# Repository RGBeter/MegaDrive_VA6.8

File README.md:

# MegaDrive
An Open-Source HardWare (OSHW) recreation of the rare Sega Mega Drive VA6.8

The design tries to be a 1:1 recreation of the original IC BD M5 PAL V6.8 board.

## Changes and Notes
- PCB altered to use surface mount MB3514

- Original VA6.8 did not populate C30, despite the MB3514 having a mono audio buffer

- Some capacitor values may be inaccurate in the video section

## Tips if you decide to make this/get it made
The dimensions are 240x191mm.

You will have to source the 2 SEGA custom chips from either a dead board or a chip dealer.

## Credits

ArcadeTV for the stripped scans:
https://circuit-board.de/forum/index.php/Thread/13913-STRIP-CLUB-PCB-Scans/
StonedDiscord for original Mega Drive Pal VA5-6.5 reproduction PCB

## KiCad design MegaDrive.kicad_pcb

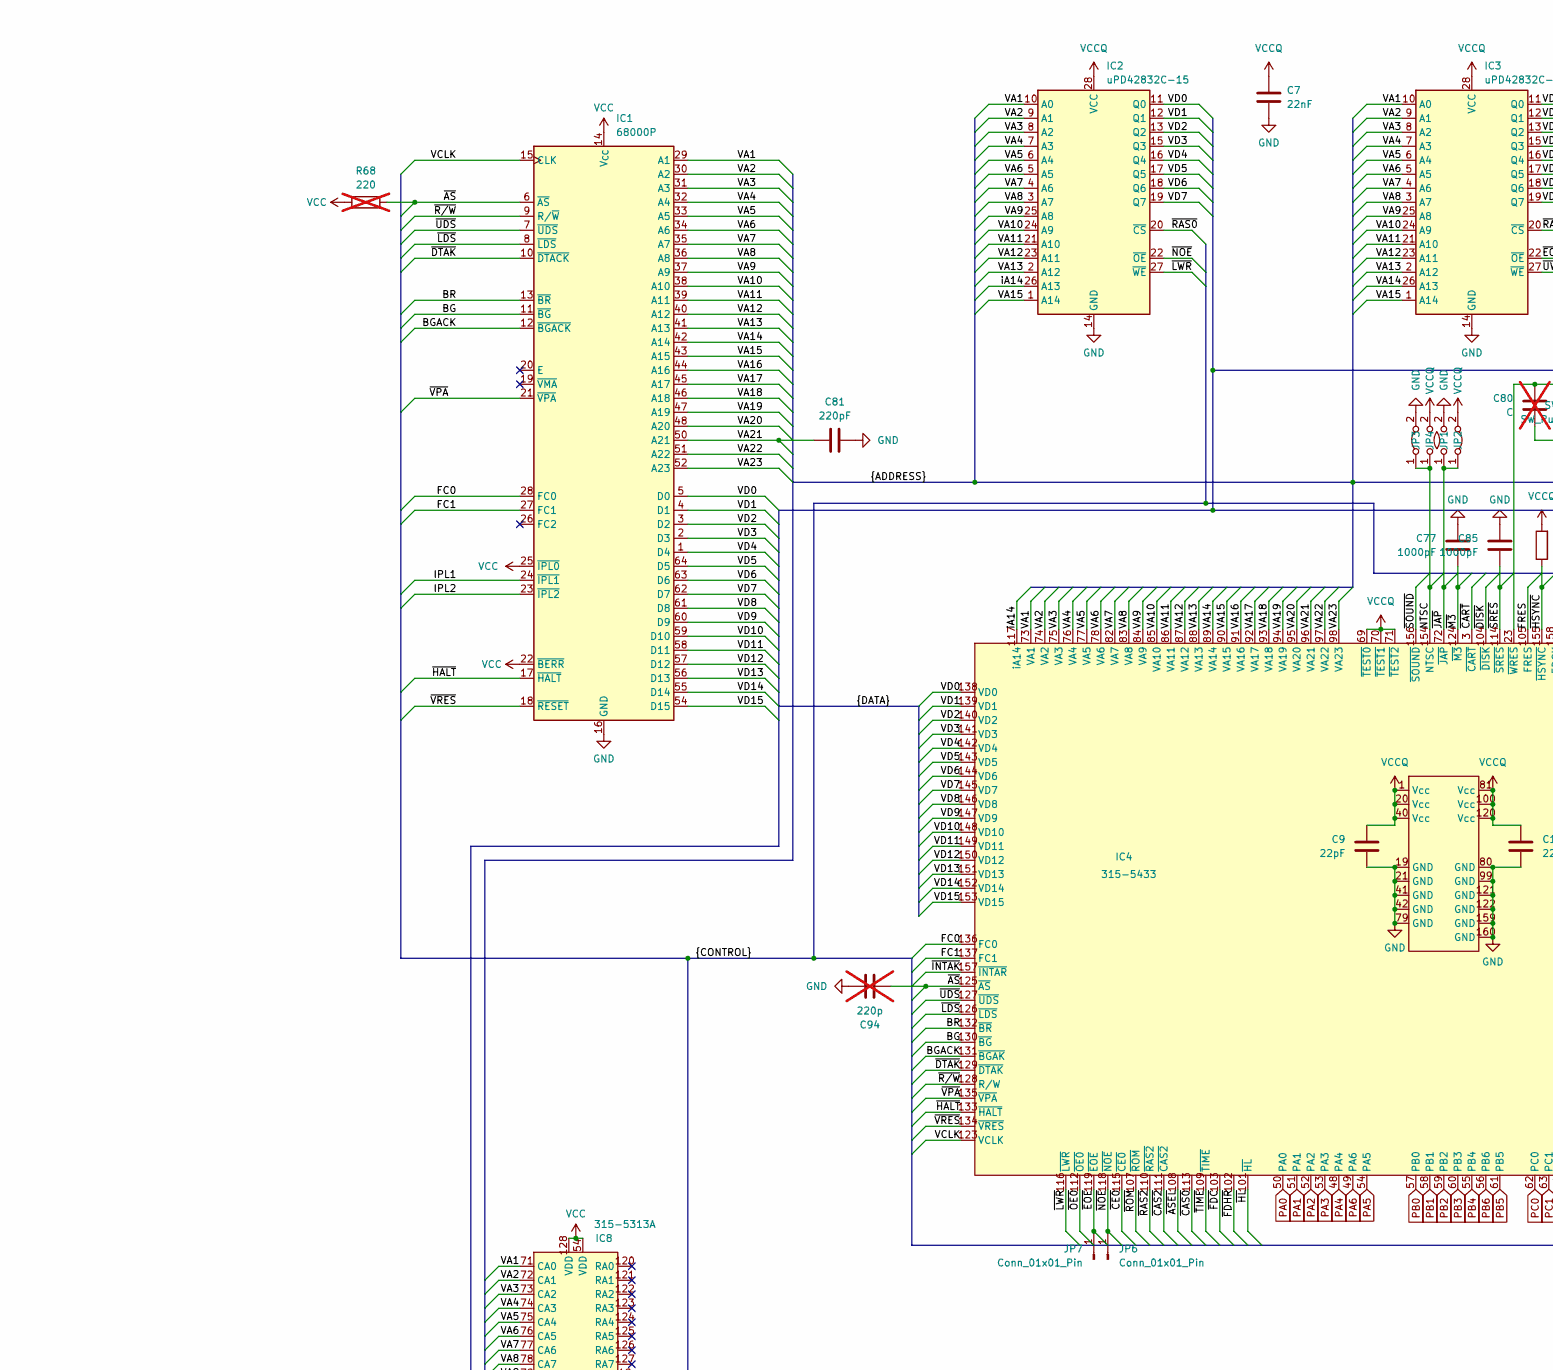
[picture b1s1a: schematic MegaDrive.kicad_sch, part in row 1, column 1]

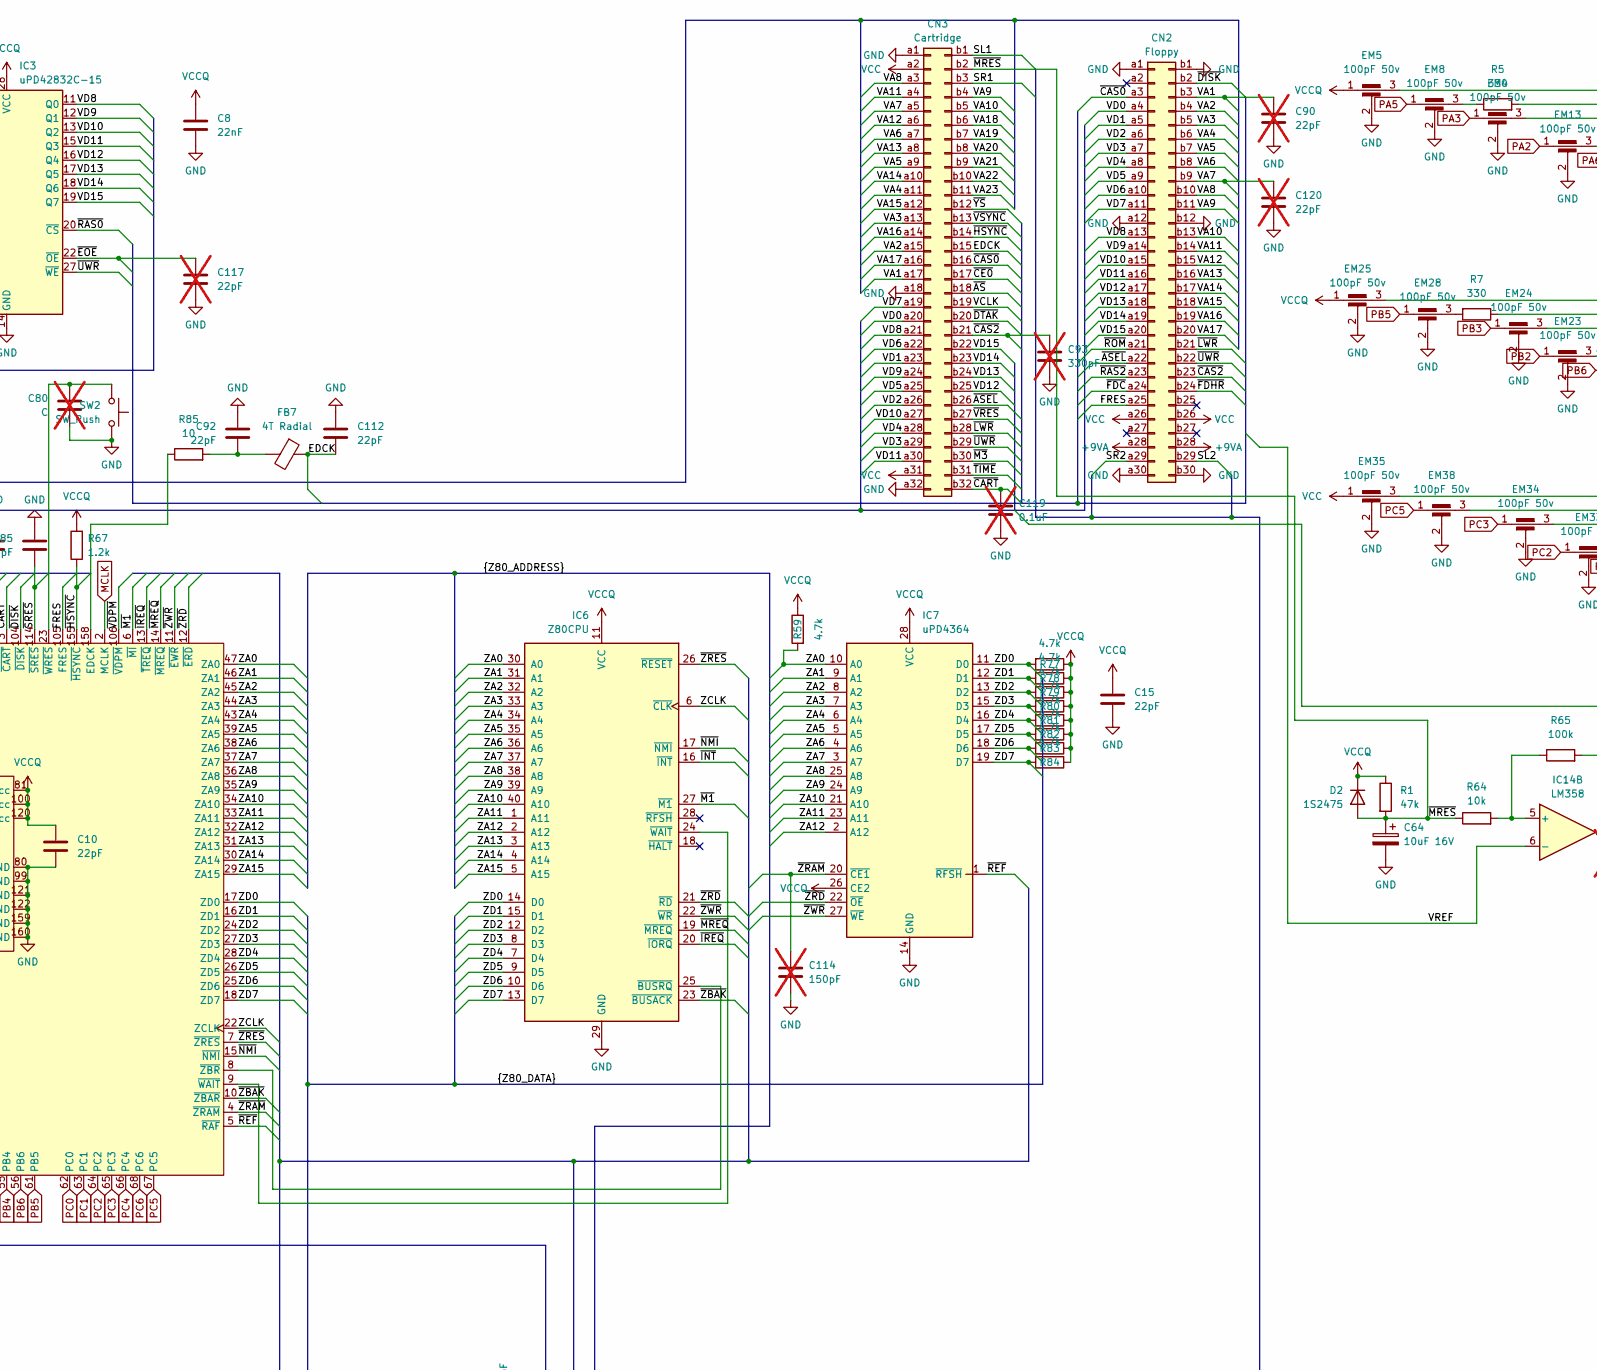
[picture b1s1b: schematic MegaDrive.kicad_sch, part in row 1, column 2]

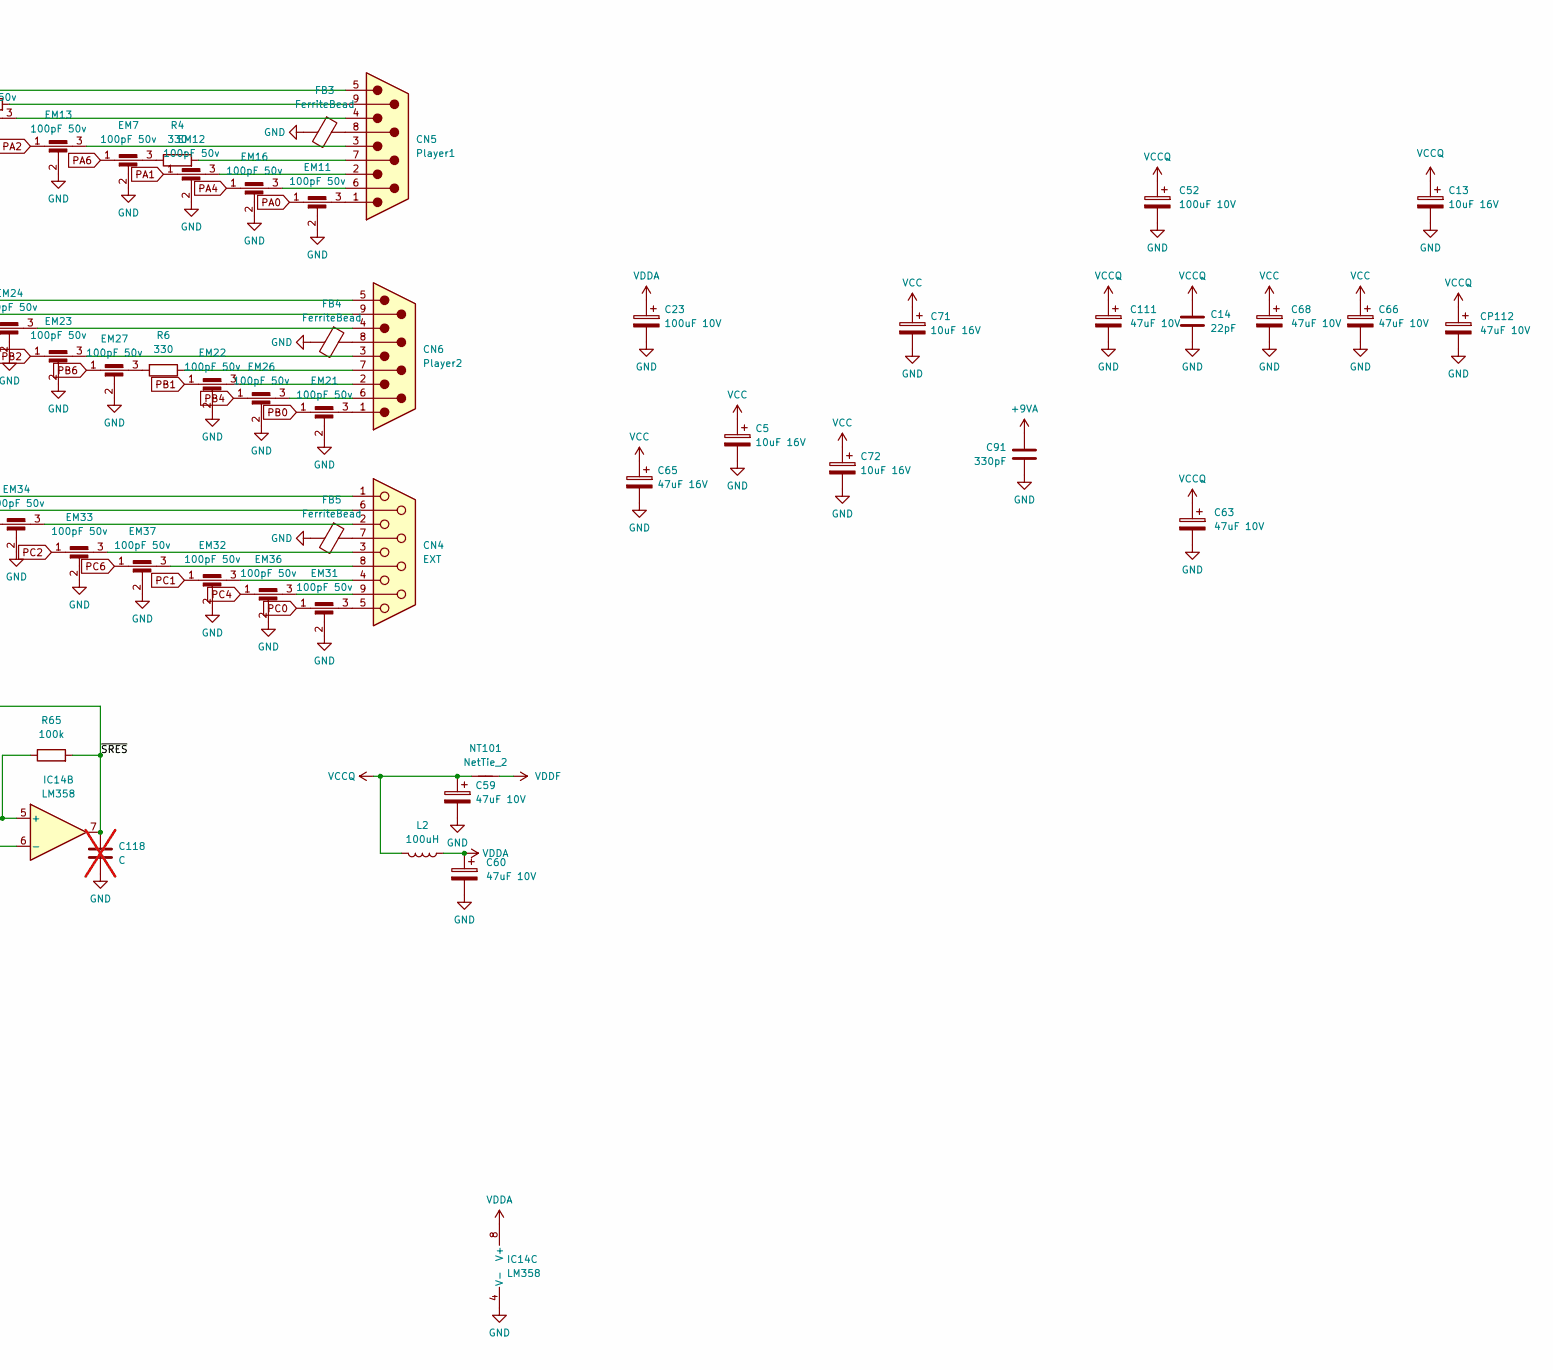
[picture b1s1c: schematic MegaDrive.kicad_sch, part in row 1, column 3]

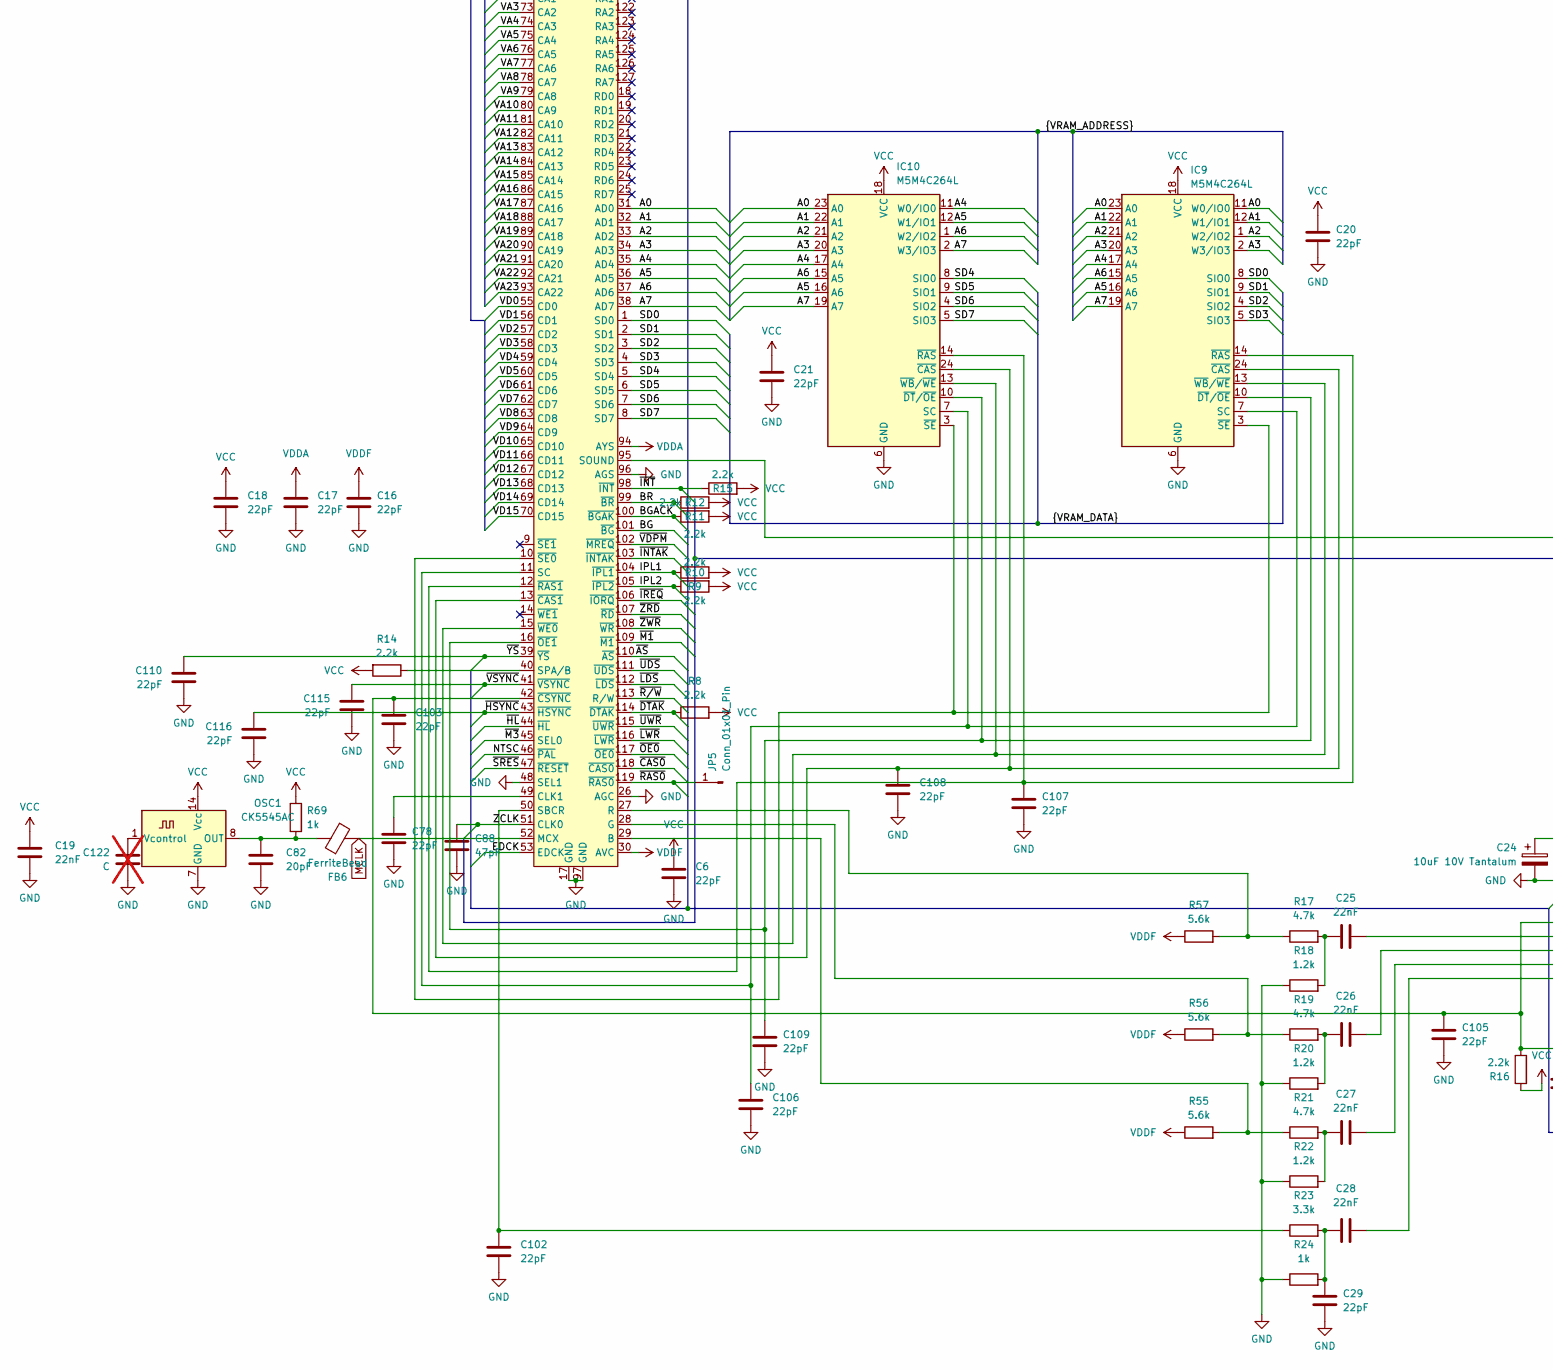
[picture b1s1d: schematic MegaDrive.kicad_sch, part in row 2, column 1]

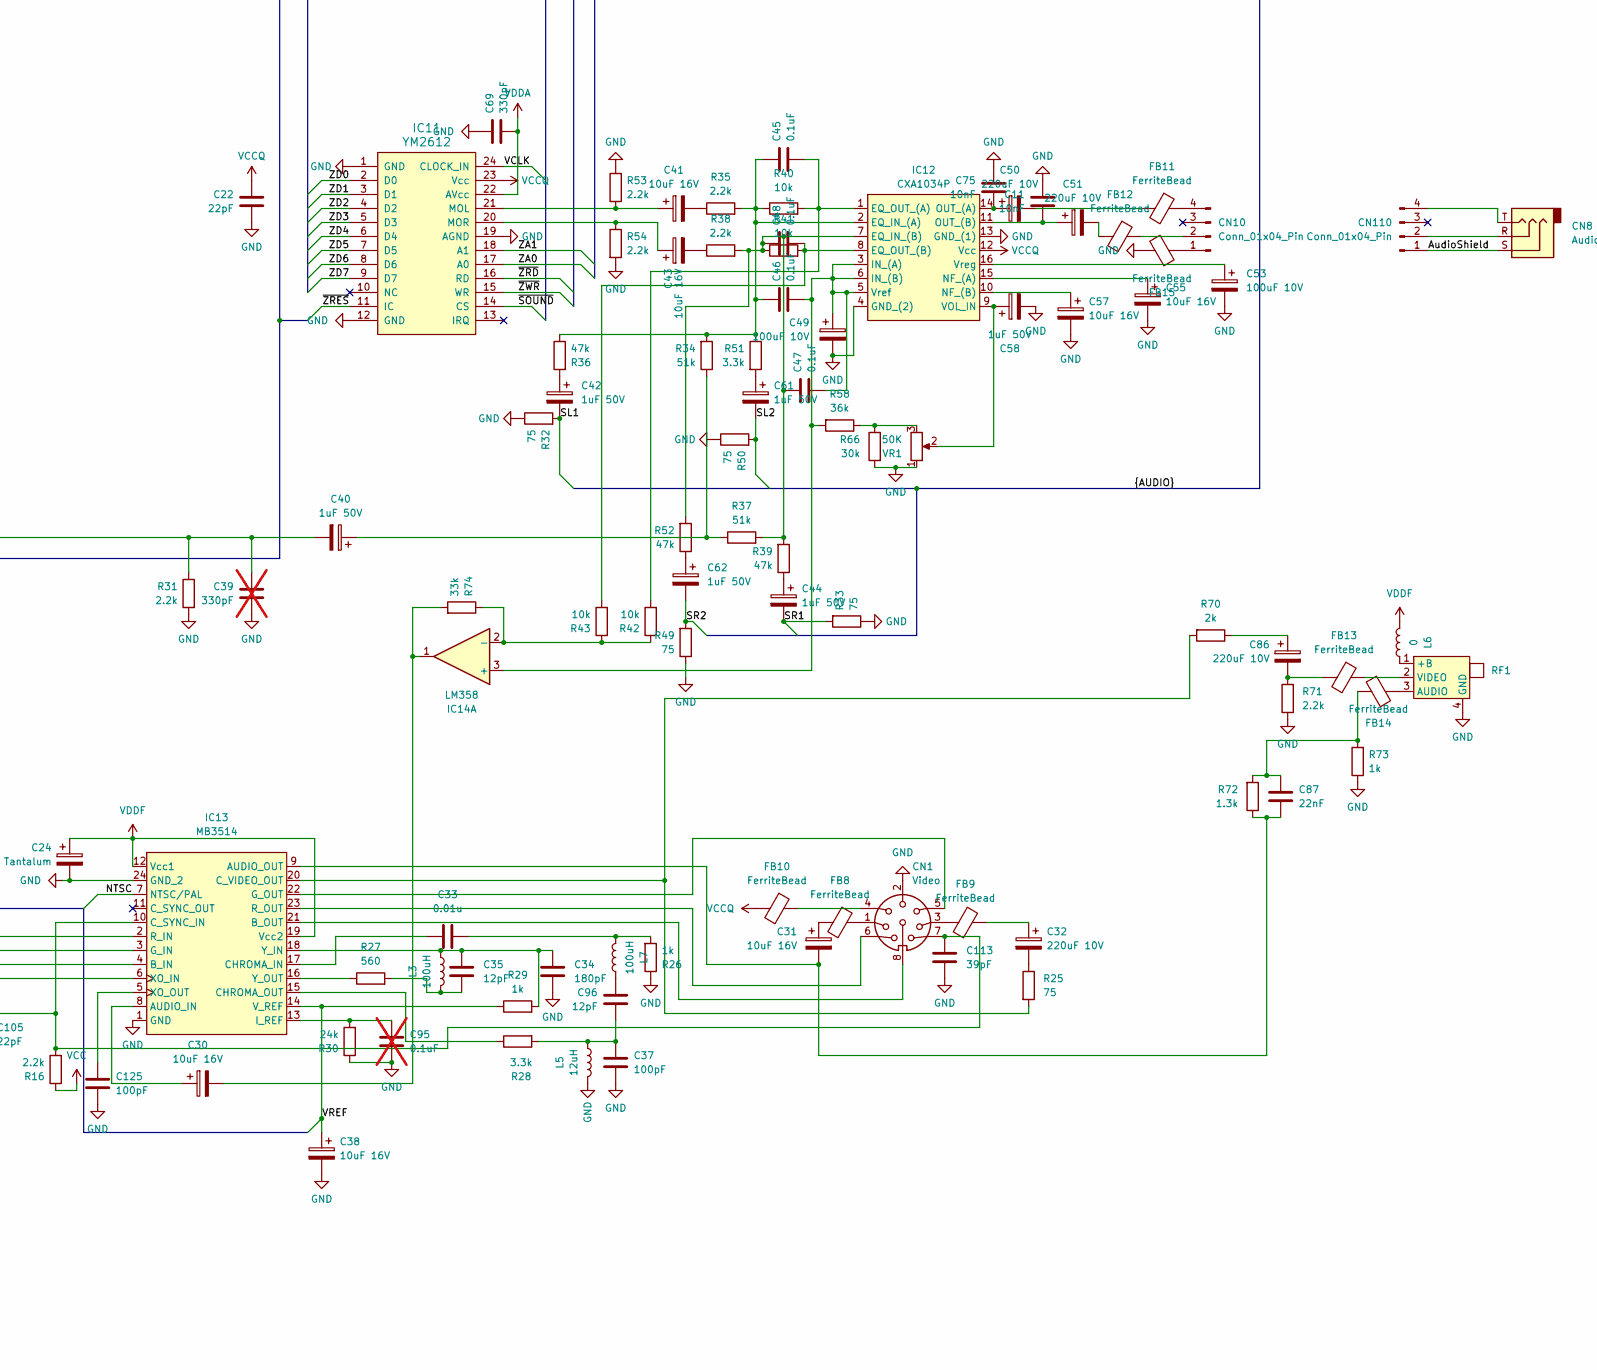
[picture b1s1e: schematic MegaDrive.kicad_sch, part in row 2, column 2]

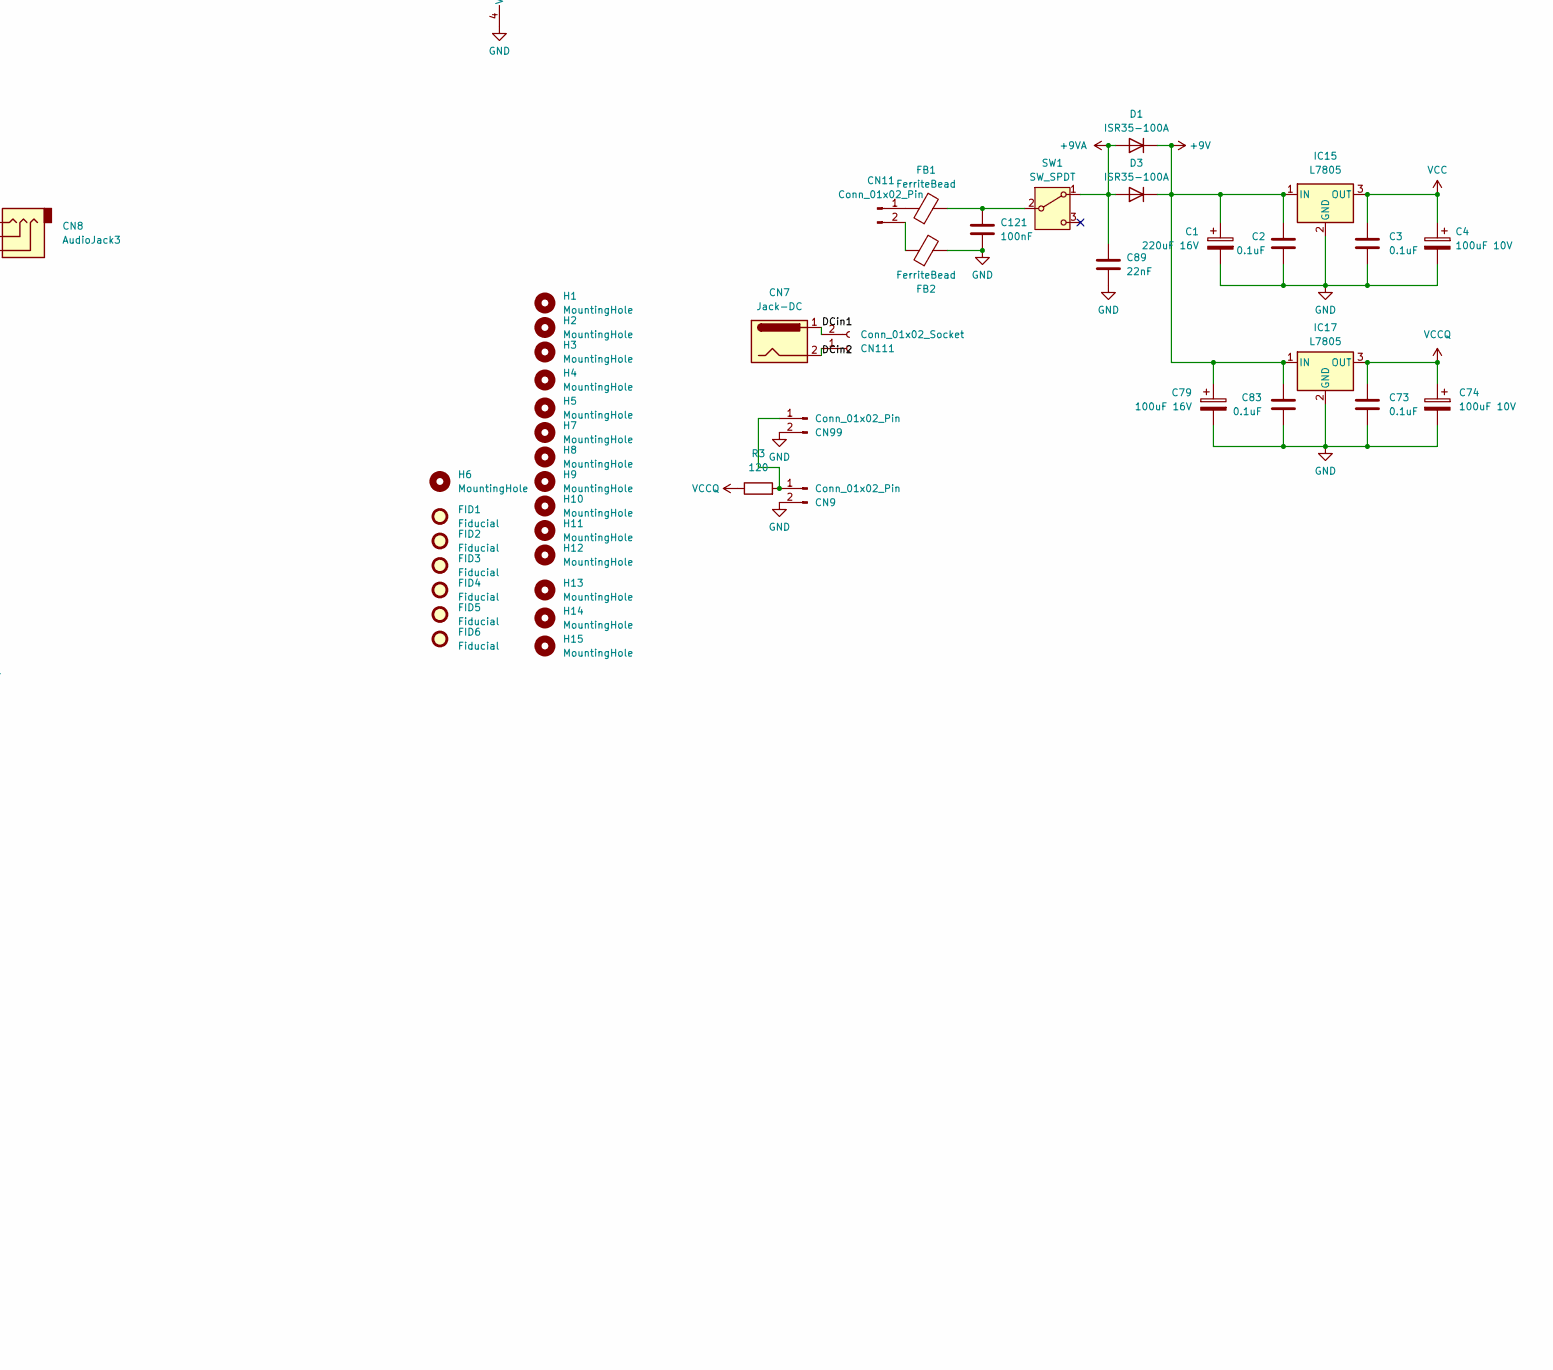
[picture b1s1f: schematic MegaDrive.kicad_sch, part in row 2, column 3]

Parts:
C1: 220uF 16V; CP_Radial_Tantal_D4.5mm_P5.00mm
C2, C3, C45, C46, C47, C48, C73, C83: 0.1uF; C_0805_2012Metric
C4, C23, C49, C52, C53, C74: 100uF 10V; CP_Radial_Tantal_D4.5mm_P5.00mm
C5, C13, C30, C31, C38, C41, C43, C55, C57, C64, C71, C72: 10uF 16V; CP_Radial_Tantal_D4.5mm_P5.00mm
C6, C9, C10, C14, C15, C16, C17, C18, C20, C21, C22, C29, C78, C92, C102, C103, C105, C106, C107, C108, C109, C110, C112, C115, C116: 22pF; C_0805_2012Metric
C7, C8, C19, C25, C26, C27, C28, C87, C89: 22nF; C_0805_2012Metric
C11, C75: 10nF; C_0805_2012Metric
C24: 10uF 10V Tantalum; CP_Radial_Tantal_D4.5mm_P5.00mm
C32, C50, C51, C86: 220uF 10V; CP_Radial_Tantal_D4.5mm_P5.00mm
C33: 0.01u; C_0805_2012Metric
C34: 180pF; C_0805_2012Metric
C35, C96: 12pF; C_0805_2012Metric
C37, C125: 100pF; C_0805_2012Metric
C39, C93: 330pF; C_0805_2012Metric; not fitted
C40, C42, C44, C58, C61, C62: 1uF 50V; CP_Radial_Tantal_D4.5mm_P5.00mm
C59, C60, C63, C66, C68, C111: 47uF 10V; CP_Radial_Tantal_D4.5mm_P5.00mm
C65: 47uF 16V; CP_Radial_Tantal_D4.5mm_P5.00mm
C69, C91: 330pF; C_0805_2012Metric
C77, C85: 1000pF; C_0805_2012Metric
C79: 100uF 16V; CP_Radial_Tantal_D4.5mm_P5.00mm
C80, C118, C122: C; C_0805_2012Metric; not fitted
C81: 220pF; C_0805_2012Metric
C82: 20pF; C_0805_2012Metric
C88: 47pF; C_0805_2012Metric
C90, C117, C120: 22pF; C_0805_2012Metric; not fitted
C94: 220p; C_0805_2012Metric; not fitted
C95, C119: 0.1uF; C_0805_2012Metric; not fitted
C113: 39pF; C_0805_2012Metric
C114: 150pF; C_0805_2012Metric; not fitted
C121: 100nF; C_0805_2012Metric
CN1: Video; DIN8Video
CN2: Floppy; Expansion
CN3: Cartridge; SEGA_2x32_Female_Vertical_THT
CN4: EXT; DSUB-9_Socket_Horizontal_P2.77x2.84mm_EdgePinOffset9.40mm
CN5: Player1; DSUB-9_Pins_Horizontal_P2.77x2.84mm_EdgePinOffset9.40mm
CN6: Player2; DSUB-9_Pins_Horizontal_P2.77x2.84mm_EdgePinOffset9.40mm
CN7: Jack-DC; BarrelJack_CUI_PJ-002A_Horizontal
CN8: AudioJack3; Jack_3.5mm
CN9, CN99: Conn_01x02_Pin; PinSocket_1x02_P2.54mm_Vertical
CN10, CN110: Conn_01x04_Pin; PinHeader_1x04_P2.00mm_Vertical
CN11: Conn_01x02_Pin; PinHeader_1x02_P2.54mm_Vertical
CN111: Conn_01x02_Socket; PinHeader_1x02_P2.54mm_Vertical
CP112: 47uF 10V; CP_Radial_Tantal_D4.5mm_P5.00mm
D1, D3: ISR35-100A; D_A-405_P5.08mm_Vertical_AnodeUp
D2: 1S2475; D_A-405_P5.08mm_Vertical_AnodeUp
EM4, EM5, EM7, EM8, EM11, EM12, EM13, EM16, EM21, EM22, EM23, EM24, EM25, EM26, EM27, EM28, EM31, EM32, EM33, EM34, EM35, EM36, EM37, EM38: 100pF 50v; Resonator-3Pin_W6.0mm_H3.0mm
FB1, FB2, FB3, FB4, FB5, FB8, FB9, FB10, FB13, FB14: FerriteBead; L_Axial_L7.0mm_D3.3mm_P5.08mm_Vertical_Fastron_MICC
FB6, FB11, FB12, FB15: FerriteBead; LairdTech_28C0236-0JW-10
FB7: 4T Radial; LairdTech_28C0236-0JW-10
FID1, FID2, FID3, FID4, FID5, FID6: Fiducial; Fiducial_1.5mm_Mask4.5mm
H1, H2, H3, H4, H5, H7, H8, H9, H10, H11, H12: MountingHole; MountingHole_3.2mm_M3
H6: MountingHole; MountingHole_4mm
H13, H14, H15: MountingHole; MountingHole_5mm
IC1: 68000P; DIP-64_W22.86mm
IC2, IC3: uPD42832C-15; DIP-28_DoubleLast
IC4: 315-5433; QFP-160_28x28_Pitch0.65mm
IC6: Z80CPU; DIP-40_W15.24mm
IC7: uPD4364; DIP-28_DoubleFirst
IC8: 315-5313A; QFP128
IC9, IC10: M5M4C264L; ZIP-24
IC11: YM2612; DIP-24_W15.24mm
IC12: CXA1034P; DIP-16_W7.62mm
IC13: MB3514; SOIC-24_CXA
IC14: LM358; DIP-8_W7.62mm
IC15, IC17: L7805; TO-220-3_Vertical
JP1: JAP; R_Axial_DIN0204_L3.6mm_D1.6mm_P5.08mm_Horizontal
JP2: ENG; R_Axial_DIN0204_L3.6mm_D1.6mm_P5.08mm_Horizontal
JP3: PAL; R_Axial_DIN0204_L3.6mm_D1.6mm_P5.08mm_Horizontal
JP4: NTSC; R_Axial_DIN0204_L3.6mm_D1.6mm_P5.08mm_Horizontal
JP5, JP6, JP7: Conn_01x01_Pin; PinSocket_1x01_P2.54mm_Vertical
L2, L3, L7: 100uH; R_Axial_DIN0204_L3.6mm_D1.6mm_P5.08mm_Horizontal
L5: 12uH; R_Axial_DIN0204_L3.6mm_D1.6mm_P5.08mm_Horizontal
L6: 0; L_Axial_L7.0mm_D3.3mm_P5.08mm_Vertical_Fastron_MICC
NT101: NetTie_2; NetTie-2_SMD_Pad2.0mm
OSC1: CK5545AC; Oscillator_DIP-14
R1, R36, R39, R52: 47k; R_0805_2012Metric
R3: 120; R_0805_2012Metric
R4, R5, R6, R7: 330; R_0805_2012Metric
R8, R9, R10, R11, R12, R14, R15, R16, R31, R35, R38, R53, R54, R71: 2.2k; R_0805_2012Metric
R17, R19, R21, R59, R77, R78, R79, R80, R81, R82, R83, R84: 4.7k; R_0805_2012Metric
R18, R20, R22, R67: 1.2k; R_0805_2012Metric
R23, R28, R51: 3.3k; R_0805_2012Metric
R24, R26, R29, R69, R73: 1k; R_0805_2012Metric
R25, R32, R33, R49, R50: 75; R_0805_2012Metric
R27: 560; R_0805_2012Metric
R30: 24k; R_0805_2012Metric
R34, R37: 51k; R_0805_2012Metric
R40, R41, R42, R43, R64: 10k; R_0805_2012Metric
R55, R56, R57: 5.6k; R_0805_2012Metric
R58: 36k; R_0805_2012Metric
R65: 100k; R_0805_2012Metric
R66: 30k; R_0805_2012Metric
R68: 220; R_0805_2012Metric; not fitted
R70: 2k; R_0805_2012Metric
R72: 1.3k; R_0805_2012Metric
R74: 33k; R_0805_2012Metric
R85: 10; R_0805_2012Metric
RF1: RFmod
SW1: SW_SPDT; SW_E-Switch_EG1224_SPDT_Angled
SW2: SW_Push; SW_Tactile_Straight_KSA0Axx1LFTR
VR1: 50K; HeadphoneVolumeSlider

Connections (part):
+9V: C1.1, C2.1, C79.1, C83.1, D1.1 (K), D3.1 (K), IC15.1 (IN), IC17.1 (IN)
+9VA: C89.1, C91.1, CN2.a28, CN2.b28, D1.2 (A), D3.2 (A), SW1.1 (A)
/A0: IC8.31 (AD0), IC9.11 (W0/IO0), IC9.23 (A0), IC10.23 (A0)
/A1: IC8.32 (AD1), IC9.12 (W1/IO1), IC9.22 (A1), IC10.22 (A1)
/A2: IC8.33 (AD2), IC9.1 (W2/IO2), IC9.21 (A2), IC10.21 (A2)
/A3: IC8.34 (AD3), IC9.2 (W3/IO3), IC9.20 (A3), IC10.20 (A3)
/A4: IC8.35 (AD4), IC9.17 (A4), IC10.11 (W0/IO0), IC10.17 (A4)
/A5: IC8.36 (AD5), IC9.16 (A6), IC10.12 (W1/IO1), IC10.16 (A6)
/A6: IC8.37 (AD6), IC9.15 (A5), IC10.1 (W2/IO2), IC10.15 (A5)
/A7: IC8.38 (AD7), IC9.19 (A7), IC10.2 (W3/IO3), IC10.19 (A7)
/AudioShield: CN8.S, CN110.1
/BG: IC1.11 (~BG), IC4.130 (~BG), IC8.101 (~BG)
/BGACK: IC1.12 (~BGACK), IC4.131 (~BGAK), IC8.100 (~BGAK), R11.1
/BR: IC1.13 (~BR), IC4.132 (~BR), IC8.99 (~BR), R12.1
/DCin1: CN7.1, CN111.2
/DCin2: CN7.2, CN111.1
/EDCK: C112.2, CN3.b15, FB7.1, IC8.53 (EDCK)
/FC0: IC1.28 (FC0), IC4.136 (FC0)
/FC1: IC1.27 (FC1), IC4.137 (FC1)
/FRES: CN2.a25, IC4.105 (FRES)
/IPL1: IC1.24 (~IPL1), IC8.104 (~IPL1), R10.1
/IPL2: IC1.23 (~IPL2), IC8.105 (~IPL2), R9.1
/NTSC: IC4.154 (NTSC), IC8.46 (~PAL), IC13.7 (NTSC/PAL), JP3.1 (A), JP4.1 (A)
/SD0: IC8.1 (SD0), IC9.8 (SIO0)
/SD1: IC8.2 (SD1), IC9.9 (SIO1)
/SD2: IC8.3 (SD2), IC9.4 (SIO2)
/SD3: IC8.4 (SD3), IC9.5 (SIO3)
/SD4: IC8.5 (SD4), IC10.8 (SIO0)
/SD5: IC8.6 (SD5), IC10.9 (SIO1)
/SD6: IC8.7 (SD6), IC10.4 (SIO2)
/SD7: IC8.8 (SD7), IC10.5 (SIO3)
/SL1: C42.2, CN3.b1, R32.2
/SL2: C61.2, CN2.b29, R50.2
/SR1: C44.2, CN3.b3, R33.2
/SR2: C62.2, CN2.a29, R49.2
/VA1: C90.1, CN2.b3, CN3.a17, IC1.29 (A1), IC2.10 (A0), IC3.10 (A0), IC4.73 (VA1), IC8.71 (CA0)
/VA2: CN2.b4, CN3.a15, IC1.30 (A2), IC2.9 (A1), IC3.9 (A1), IC4.74 (VA2), IC8.72 (CA1)
/VA3: CN2.b5, CN3.a13, IC1.31 (A3), IC2.8 (A2), IC3.8 (A2), IC4.75 (VA3), IC8.73 (CA2)
/VA4: CN2.b6, CN3.a11, IC1.32 (A4), IC2.7 (A3), IC3.7 (A3), IC4.76 (VA4), IC8.74 (CA3)
/VA5: CN2.b7, CN3.a9, IC1.33 (A5), IC2.6 (A4), IC3.6 (A4), IC4.77 (VA5), IC8.75 (CA4)
/VA6: CN2.b8, CN3.a7, IC1.34 (A6), IC2.5 (A5), IC3.5 (A5), IC4.78 (VA6), IC8.76 (CA5)
/VA7: C120.1, CN2.b9, CN3.a5, IC1.35 (A7), IC2.4 (A6), IC3.4 (A6), IC4.82 (VA7), IC8.77 (CA6)
/VA8: CN2.b10, CN3.a3, IC1.36 (A8), IC2.3 (A7), IC3.3 (A7), IC4.83 (VA8), IC8.78 (CA7)
/VA9: CN2.b11, CN3.b4, IC1.37 (A9), IC2.25 (A8), IC3.25 (A8), IC4.84 (VA9), IC8.79 (CA8)
/VA10: CN2.b13, CN3.b5, IC1.38 (A10), IC2.24 (A9), IC3.24 (A9), IC4.85 (VA10), IC8.80 (CA9)
/VA11: CN2.b14, CN3.a4, IC1.39 (A11), IC2.21 (A10), IC3.21 (A10), IC4.86 (VA11), IC8.81 (CA10)
/VA12: CN2.b15, CN3.a6, IC1.40 (A12), IC2.23 (A11), IC3.23 (A11), IC4.87 (VA12), IC8.82 (CA11)
/VA13: CN2.b16, CN3.a8, IC1.41 (A13), IC2.2 (A12), IC3.2 (A12), IC4.88 (VA13), IC8.83 (CA12)
/VA14: CN2.b17, CN3.a10, IC1.42 (A14), IC3.26 (A13), IC4.89 (VA14), IC8.84 (CA13)
/VA15: CN2.b18, CN3.a12, IC1.43 (A15), IC2.1 (A14), IC3.1 (A14), IC4.90 (VA15), IC8.85 (CA14)
/VA16: CN2.b19, CN3.a14, IC1.44 (A16), IC4.91 (VA16), IC8.86 (CA15)
/VA17: CN2.b20, CN3.a16, IC1.45 (A17), IC4.92 (VA17), IC8.87 (CA16)
/VA18: CN3.b6, IC1.46 (A18), IC4.93 (VA18), IC8.88 (CA17)
/VA19: CN3.b7, IC1.47 (A19), IC4.94 (VA19), IC8.89 (CA18)
/VA20: CN3.b8, IC1.48 (A20), IC4.95 (VA20), IC8.90 (CA19)
/VA21: C81.2, CN3.b9, IC1.50 (A21), IC4.96 (VA21), IC8.91 (CA20)
/VA22: CN3.b10, IC1.51 (A22), IC4.97 (VA22), IC8.92 (CA21)
/VA23: CN3.b11, IC1.52 (A23), IC4.98 (VA23), IC8.93 (CA22)
/VCLK: CN3.b19, IC1.15 (CLK), IC4.123 (VCLK), IC11.24 (CLOCK_IN)
/VD0: CN2.a4, CN3.a20, IC1.5 (D0), IC2.11 (Q0), IC4.138 (VD0), IC8.55 (CD0)
/VD1: CN2.a5, CN3.a23, IC1.4 (D1), IC2.12 (Q1), IC4.139 (VD1), IC8.56 (CD1)
/VD2: CN2.a6, CN3.a26, IC1.3 (D2), IC2.13 (Q2), IC4.140 (VD2), IC8.57 (CD2)
/VD3: CN2.a7, CN3.a29, IC1.2 (D3), IC2.15 (Q3), IC4.141 (VD3), IC8.58 (CD3)
/VD4: CN2.a8, CN3.a28, IC1.1 (D4), IC2.16 (Q4), IC4.142 (VD4), IC8.59 (CD4)
/VD5: CN2.a9, CN3.a25, IC1.64 (D5), IC2.17 (Q5), IC4.143 (VD5), IC8.60 (CD5)
/VD6: CN2.a10, CN3.a22, IC1.63 (D6), IC2.18 (Q6), IC4.144 (VD6), IC8.61 (CD6)
/VD7: CN2.a11, CN3.a19, IC1.62 (D7), IC2.19 (Q7), IC4.145 (VD7), IC8.62 (CD7)
/VD8: CN2.a13, CN3.a21, IC1.61 (D8), IC3.11 (Q0), IC4.146 (VD8), IC8.63 (CD8)
/VD9: CN2.a14, CN3.a24, IC1.60 (D9), IC3.12 (Q1), IC4.147 (VD9), IC8.64 (CD9)
/VD10: CN2.a15, CN3.a27, IC1.59 (D10), IC3.13 (Q2), IC4.148 (VD10), IC8.65 (CD10)
/VD11: CN2.a16, CN3.a30, IC1.58 (D11), IC3.15 (Q3), IC4.149 (VD11), IC8.66 (CD11)
/VD12: CN2.a17, CN3.b25, IC1.57 (D12), IC3.16 (Q4), IC4.150 (VD12), IC8.67 (CD12)
/VD13: CN2.a18, CN3.b24, IC1.56 (D13), IC3.17 (Q5), IC4.151 (VD13), IC8.68 (CD13)
/VD14: CN2.a19, CN3.b23, IC1.55 (D14), IC3.18 (Q6), IC4.152 (VD14), IC8.69 (CD14)
/VD15: CN2.a20, CN3.b22, IC1.54 (D15), IC3.19 (Q7), IC4.153 (VD15), IC8.70 (CD15)
/VREF: C38.1, IC13.14 (V_REF), IC14.6 (-), R29.1
/ZA0: IC4.47 (ZA0), IC6.30 (A0), IC7.10 (A0), IC11.17 (A0), R59.2
/ZA1: IC4.46 (ZA1), IC6.31 (A1), IC7.9 (A1), IC11.18 (A1)
/ZA2: IC4.45 (ZA2), IC6.32 (A2), IC7.8 (A2)
/ZA3: IC4.44 (ZA3), IC6.33 (A3), IC7.7 (A3)
/ZA4: IC4.43 (ZA4), IC6.34 (A4), IC7.6 (A4)
/ZA5: IC4.39 (ZA5), IC6.35 (A5), IC7.5 (A5)
/ZA6: IC4.38 (ZA6), IC6.36 (A6), IC7.4 (A6)
/ZA7: IC4.37 (ZA7), IC6.37 (A7), IC7.3 (A7)
/ZA8: IC4.36 (ZA8), IC6.38 (A8), IC7.25 (A8)
/ZA9: IC4.35 (ZA9), IC6.39 (A9), IC7.24 (A9)
/ZA10: IC4.34 (ZA10), IC6.40 (A10), IC7.21 (A10)
/ZA11: IC4.33 (ZA11), IC6.1 (A11), IC7.23 (A11)
/ZA12: IC4.32 (ZA12), IC6.2 (A12), IC7.2 (A12)
/ZA13: IC4.31 (ZA13), IC6.3 (A13)
/ZA14: IC4.30 (ZA14), IC6.4 (A14)
/ZA15: IC4.29 (ZA15), IC6.5 (A15)
/ZCLK: C88.1, IC4.22 (ZCLK), IC6.6 (~CLK), IC8.51 (CLK0)
/ZD0: IC4.17 (ZD0), IC6.14 (D0), IC7.11 (D0), IC11.2 (D0), R77.2
/ZD1: IC4.16 (ZD1), IC6.15 (D1), IC7.12 (D1), IC11.3 (D1), R78.2
/ZD2: IC4.24 (ZD2), IC6.12 (D2), IC7.13 (D2), IC11.4 (D2), R79.2
/ZD3: IC4.27 (ZD3), IC6.8 (D3), IC7.15 (D3), IC11.5 (D3), R80.2
/ZD4: IC4.28 (ZD4), IC6.7 (D4), IC7.16 (D4), IC11.6 (D4), R81.2
/ZD5: IC4.26 (ZD5), IC6.9 (D5), IC7.17 (D5), IC11.7 (D5), R82.2
/ZD6: IC4.25 (ZD6), IC6.10 (D6), IC7.18 (D6), IC11.8 (D6), R83.2
/ZD7: IC4.18 (ZD7), IC6.13 (D7), IC7.19 (D7), IC11.9 (D7), R84.2
/iA14: IC2.26 (A13), IC4.117 (iA14)
/~ASEL: CN2.a22, CN3.b26, IC4.108
/~AS: C94.2, CN3.b18, IC1.6 (~AS), IC4.125 (~AS), IC8.110 (~AS), R68.1
/~CART: C119.1, CN3.b32, IC4.3 (~CART)
/~CAS0: CN2.a3, CN3.b16, IC4.113, IC8.118 (~CAS0)
/~CAS2: C93.1, CN2.b23, CN3.b21, IC4.111 (~CAS2)
/~CE0: CN3.b17, IC4.115 (~CE0)
/~DISK: CN2.b2, IC4.104 (~DISK)
/~DTAK: CN3.b20, IC1.10 (~DTACK), IC4.129 (~DTAK), IC8.114 (~DTAK), R8.1
/~EOE: C117.1, IC3.22 (~OE), IC4.119 (~EOE), JP7.1
/~FDC: CN2.a24, IC4.103
/~FDHR: CN2.b24, IC4.102
/~HALT: IC1.17 (~HALT), IC4.133 (~HALT)
/~HL: IC4.101 (~HL), IC8.44 (~HL)
/~HSYNC: C116.1, CN3.b14, IC4.155 (~HSYNC), IC8.43 (~HSYNC), R67.1
/~INTAK: IC4.157 (~INTAR), IC8.103 (~INTAK)
/~INT: IC6.16 (~INT), IC8.98 (~INT), R15.1
/~IREQ: IC4.13 (~TREQ), IC6.20 (~IORQ), IC8.106 (~IORQ)
/~JAP: IC4.72 (~JAP), JP1.1 (A), JP2.1 (A)
/~LDS: IC1.8 (~LDS), IC4.126 (~LDS), IC8.112 (~LDS)
/~LWR: CN2.b21, CN3.b28, IC2.27 (~WE), IC4.116 (~LWR), IC8.116 (~LWR)
/~M1: IC4.6 (~MI), IC6.27 (~M1), IC8.109 (~M1)
/~M3: C77.2, CN3.b30, IC4.124 (~M3), IC8.45 (SEL0)
/~MREQ: IC4.14 (~MREQ), IC6.19 (~MREQ)
/~MRES: C64.1, CN3.b2, D2.2 (A), R1.2, R64.1
/~NMI: IC4.15 (~NMI), IC6.17 (~NMI)
/~NOE: IC2.22 (~OE), IC4.118 (~NOE), JP6.1
/~OE0: IC4.112 (~OE0), IC8.117 (~OE0)
/~RAS0: IC2.20 (~CS), IC3.20 (~CS), IC8.119 (~RAS0), JP5.1
/~RAS2: CN2.a23, IC4.110 (~RAS2)
/~REF: IC4.5 (~RAF), IC7.1 (~RFSH)
/~ROM: CN2.a21, IC4.107 (~ROM)
/~R/W: IC1.9 (R/~W), IC4.128 (R/W), IC8.113 (R/W)
/~SOUND: IC4.156 (~SOUND), IC11.14 (CS)
/~SRES: C85.2, C118.1, IC4.114 (~SRES), IC8.47 (~RESET), IC14.7, R65.2
/~TIME: CN3.b31, IC4.109 (~TIME)
/~UDS: IC1.7 (~UDS), IC4.127 (~UDS), IC8.111 (~UDS)
/~UWR: CN2.b22, CN3.b29, IC3.27 (~WE), IC8.115 (~UWR)
/~VDPM: IC4.106 (~VDPM), IC8.102 (~MREQ)
/~VPA: IC1.21 (~VPA), IC4.135 (~VPA)
/~VRES: CN3.b27, IC1.18 (~RESET), IC4.134 (~VRES)
/~VSYNC: C115.1, CN3.b13, IC8.41 (~VSYNC)
/~YS: C110.1, CN3.b12, IC8.39 (~YS)
/~ZBAK: IC4.10 (~ZBAR), IC6.23 (~BUSACK)
/~ZRAM: C114.1, IC4.4 (~ZRAM), IC7.20 (~CE1)
/~ZRD: IC4.12 (~ERD), IC6.21 (~RD), IC7.22 (~OE), IC8.107 (~RD), IC11.16 (RD)
/~ZRES: IC4.7 (~ZRES), IC6.26 (~RESET), IC11.11 (IC)
/~ZWR: IC4.11 (~EWR), IC6.22 (~WR), IC7.27 (~WE), IC8.108 (~WR), IC11.15 (WR)
GND: C1.2, C2.2, C3.2, C4.2, C5.2, C6.2, C7.2, C8.2, C9.2, C10.2, C11.2, C13.2, C14.2, C15.2, C16.2, C17.2, C18.2, C19.2, C20.2, C21.2, C22.2, C23.2, C24.2, C29.2, C34.2, C37.2, C38.2, C39.2, C49.2, C52.2, C53.2, C55.2, C57.2, C58.2, C59.2, C60.2, C63.2, C64.2, C65.2, C66.2, C68.2, C69.1, C71.2, C72.2, C73.2, C74.2, C75.2, C77.1, C78.2, C79.2, C80.2, C81.1, C82.2, C83.2, C85.1, C88.2, C89.2, C90.2, C91.2, C92.1, C93.2, C94.1, C95.2, C102.2, C103.2, C105.2, C106.2, C107.2, C108.2, C109.2, C110.2, C111.2, C112.1, C113.2, C114.2, C115.2, C116.2, C117.2, C118.2, C119.2, C120.2, C121.2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
MCLK: FB6.2, IC4.2 (MCLK), IC8.52 (MCX)
unnamed: C25.1, R17.2, R18.2
unnamed: C26.1, R19.2, R20.2
unnamed: C27.1, R21.2, R22.2
unnamed: C28.2, C29.1, R23.2, R24.2
unnamed: C30.2, IC14.1, R74.2
unnamed: C31.1, FB8.2
unnamed: C32.1, FB9.2
unnamed: C32.2, R25.1
unnamed: C33.2, L7.2, R26.2
unnamed: C35.2, L3.1, R27.2
unnamed: C37.1, C96.2, L5.2, R28.2
unnamed: C40.1, R34.1, R37.1
unnamed: C41.2, R35.1
unnamed: C42.1, R36.2
unnamed: C43.2, R38.1
unnamed: C44.1, R39.1
unnamed: C50.2, FB11.2
unnamed: C51.2, FB12.2
unnamed: C61.1, R51.2
unnamed: C62.1, R52.1
unnamed: C86.1, R70.1
unnamed: C86.2, FB13.2, R71.2
unnamed: C87.1, FB14.1, R72.2, R73.2
unnamed: C92.2, FB7.2, R85.2
unnamed: C96.1, L7.1
unnamed: CN1.1, FB8.1
unnamed: CN1.3, FB9.1
unnamed: CN1.4, FB10.1
unnamed: CN4.1, EM35.3
unnamed: CN4.2, EM34.3
unnamed: CN4.3, EM33.3
unnamed: CN4.4, EM32.3
unnamed: CN4.5, EM31.3
unnamed: CN4.6, EM38.3
unnamed: CN4.7, FB5.1
unnamed: CN4.8, EM37.3
unnamed: CN4.9, EM36.3
unnamed: CN5.1, EM11.3
unnamed: CN5.2, EM12.3
unnamed: CN5.3, EM13.3
unnamed: CN5.4, EM4.3
unnamed: CN5.5, EM5.3
unnamed: CN5.6, EM16.3
unnamed: CN5.7, R4.2
unnamed: CN5.8, FB3.1
unnamed: CN5.9, R5.2
unnamed: CN6.1, EM21.3
unnamed: CN6.2, EM22.3
unnamed: CN6.3, EM23.3
unnamed: CN6.4, EM24.3
unnamed: CN6.5, EM25.3
unnamed: CN6.6, EM26.3
unnamed: CN6.7, R6.1
unnamed: CN6.8, FB4.1
unnamed: CN6.9, R7.1
unnamed: CN9.1, CN99.1, R3.2
unnamed: CN10.1, FB15.1
unnamed: CN10.2, FB12.1
unnamed: CN10.4, FB11.1
unnamed: CN11.1, FB1.1
unnamed: CN11.2, FB2.1
unnamed: CN8.R, CN110.2
unnamed: CN8.T, CN110.4
unnamed: EM7.3, R4.1
unnamed: EM8.3, R5.1
unnamed: EM27.3, R6.2
unnamed: EM28.3, R7.2
unnamed: IC4.158 (EDCK), R85.1
unnamed: IC4.9 (~WAIT), IC6.24 (~WAIT)
unnamed: C80.1, IC4.23 (~WRES), SW2.2
unnamed: IC4.8 (~ZBR), IC6.25 (~BUSRQ)
unnamed: IC8.29 (B), R21.1, R55.2
unnamed: C78.1, IC8.49 (CLK1)
unnamed: IC8.28 (G), R19.1, R56.2
unnamed: IC8.27 (R), R17.1, R57.2
unnamed: C102.1, IC8.50 (SBCR), R23.1
unnamed: C39.1, C40.2, IC8.95 (SOUND), R31.1
unnamed: IC8.40 (SPA/B), R14.1
unnamed: C106.1, IC8.11 (SC), IC9.7 (SC), IC10.7 (SC)
unnamed: C108.1, IC8.13 (~CAS1), IC9.24 (~CAS), IC10.24 (~CAS)
unnamed: C109.1, IC8.16 (~OE1), IC9.10 (~DT/~OE), IC10.10 (~DT/~OE)
unnamed: C107.1, IC8.12 (~RAS1), IC9.14 (~RAS), IC10.14 (~RAS)
unnamed: IC8.10 (~SE0), IC9.3 (~SE), IC10.3 (~SE)
unnamed: IC8.15 (~WE0), IC9.13 (~WB/~WE), IC10.13 (~WB/~WE)
unnamed: C41.1, IC11.21 (MOL), R53.1
unnamed: C43.1, IC11.20 (MOR), R54.1
unnamed: C45.1, C46.1, IC12.2 (EQ_IN_(A)), R34.2, R35.2, R36.1, R40.1, R51.1
unnamed: C47.1, C48.1, IC12.7 (EQ_IN_(B)), R37.2, R38.2, R39.2, R41.1, R52.2
unnamed: C45.2, IC12.1 (EQ_OUT_(A)), R40.2, R42.2
unnamed: C48.2, IC12.8 (EQ_OUT_(B)), R41.2, R43.2
unnamed: C46.2, C47.2, C49.1, IC12.3 (IN_(A)), IC12.5 (Vref), IC12.6 (IN_(B)), IC14.3 (+), R58.2
unnamed: C55.1, IC12.15 (NF_(A))
unnamed: C57.1, IC12.10 (NF_(B))
unnamed: C50.1, C75.1, IC12.14 (OUT_(A))
unnamed: C11.1, C51.1, IC12.11 (OUT_(B))
unnamed: C58.1, IC12.9 (VOL_IN), VR1.2
unnamed: C53.1, IC12.16 (Vreg)
unnamed: C30.1, IC13.8 (AUDIO_IN)
unnamed: C31.2, C87.2, IC13.9 (AUDIO_OUT), R72.1
unnamed: C27.2, IC13.4 (B_IN)
unnamed: CN1.8, IC13.21 (B_OUT)
unnamed: C33.1, IC13.17 (CHROMA_IN)
unnamed: IC13.15 (CHROMA_OUT), R28.1
unnamed: C103.1, C105.1, C113.1, CN1.7, IC8.42 (~CSYNC), IC13.10 (C_SYNC_IN), R16.2
unnamed: IC13.20 (C_VIDEO_OUT), R25.2, R70.2
unnamed: C26.2, IC13.3 (G_IN)
unnamed: CN1.5, IC13.22 (G_OUT)
unnamed: C95.1, IC13.13 (I_REF), R30.2
unnamed: C25.2, IC13.2 (R_IN)
unnamed: CN1.6, IC13.23 (R_OUT)
unnamed: C28.1, IC13.6 (XO_IN)
unnamed: C125.1, IC13.5 (XO_OUT)
unnamed: C34.1, C35.1, IC13.18 (Y_IN), L3.2, R29.2
unnamed: IC13.16 (Y_OUT), R27.1
unnamed: IC14.2 (-), R42.1, R43.1, R74.1
unnamed: IC14.5 (+), R64.2, R65.1
unnamed: C82.1, FB6.1, OSC1.8 (OUT), R69.1
unnamed: C122.1, OSC1.1 (Vcontrol)
unnamed: R58.1, R66.1, VR1.3
unnamed: L6.2, RF1.1 (+B)
unnamed: FB14.2, RF1.3 (AUDIO)
unnamed: FB13.1, RF1.2 (VIDEO)
unnamed: C121.1, FB1.2, SW1.2 (B)
PA0: EM11.1, IC4.50 (PA0)
PA1: EM12.1, IC4.51 (PA1)
PA2: EM13.1, IC4.52 (PA2)
PA3: EM4.1, IC4.53 (PA3)
PA4: EM16.1, IC4.48 (PA4)
PA5: EM8.1, IC4.54 (PA5)
PA6: EM7.1, IC4.49 (PA6)
PB0: EM21.1, IC4.57 (PB0)
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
